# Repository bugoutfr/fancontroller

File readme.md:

# FanController

Standalone four-channel PWM fan controller based on the ESP32, with a local Windows client for Bluetooth Low Energy configuration and monitoring. No cloud service, account, or backend is required.

## Features

- Two 10 kΩ / B3950 NTC sensors, each assigned to two fans.
- Independent temperature profiles with linear interpolation.
- Per-fan PWM override and tachometer (TACH) speed measurement.
- Thermal protection takes priority over manual settings.
- Settings are applied in RAM and saved explicitly to NVS for persistence across restarts.
- BLE pairing is physically authorized with the ESP32 BOOT button.
- Windows client with profile charts, local 30-day temperature/RPM history, and system-tray operation.
- Automatic reconnection to the last Windows-paired controller. Interrupted writes are never replayed.

Temperature control runs on the ESP32 without a computer or Bluetooth connection. The percentage controls PWM duty cycle; it is not closed-loop RPM control.

## Project layout

| Directory | Contents | Guide |
|---|---|---|
| [esp32](esp32/) | Arduino / PlatformIO firmware, hardware configuration, and C++ tests | [Firmware guide](esp32/README.md) |
| [windows](windows/) | WinUI 3 / .NET 10 client for Windows 11 x64 and .NET tests | [Windows client guide](windows/README.md) |
| [hardware](hardware/) | KiCad prototype board CAD | [Hardware guide](hardware/README.md) |

The KiCad board is explicitly a work in progress and is **not ready for fabrication**. It does not replace the firmware wiring diagram.

## Quick start

### ESP32

From `esp32`, with PlatformIO installed:

```powershell
pio run -e esp32dev
pio run -e esp32dev -t upload
pio device monitor -b 115200
```

Review the [wiring and power precautions](esp32/README.md#wiring) before uploading. Do not connect powered USB and 5 V to VIN together unless supply isolation has been confirmed.

### Windows

From `windows`, with the prerequisites in the [Windows guide](windows/README.md):

```powershell
dotnet restore .\FanController.sln
dotnet test .\tests\FanController.Tests\FanController.Tests.csproj -c Release
dotnet publish .\src\FanController.App\FanController.App.csproj -c Release -r win-x64 -p:Platform=x64 -o .\artifacts\desktop
.\artifacts\desktop\FanController.App.exe
```

Distribute the complete publish directory, not only the executable.

## First pairing

1. Start the ESP32 normally, hold **BOOT for 2 seconds**, then release to open a 60-second pairing window.
2. Search for the controller in the Windows client and connect/pair.
3. Subsequent connections reuse the stored keys.

Holding **BOOT for 10 seconds** and releasing revokes the owner. Remove the Windows pairing before pairing again. Do not hold BOOT during reset. **Just Works** encrypts the link but does not protect the first pairing against active interception; pair in a trusted environment.

## License

This project is distributed under the permissive [MIT License](LICENSE). Third-party dependencies retain their own licenses; see the relevant dependency documentation.

## Tests

- Firmware and pairing tests: [ESP32 guide](esp32/README.md#build-and-test).
- Windows tests: [Windows guide](windows/README.md#build-test-and-run).

Host tests do not replace checking sensors, PWM/TACH outputs, Bluetooth, and power behavior on real hardware.

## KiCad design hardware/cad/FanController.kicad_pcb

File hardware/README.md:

# KiCad prototype board (P1)

> **Work in progress — NOT FOR FABRICATION.** A connected schematic and fully routed PCB are available, but the SATA connector mechanics and electrical qualifications still need review. No manufacturing outputs are approved.

## Open the design

Open `cad\FanController.kicad_pro` in **KiCad 10.0.7**.

- `cad\FanController.kicad_sch`: native A2 schematic with power, USB-UART, BOOT/RESET, four PWM/TACH channels, and two NTC inputs.
- `cad\FanController.kicad_pcb`: native two-layer board, 74 × 54 mm outline, four M2 mounting holes, and 71 electrical components.
- `cad\FanController.pretty\SATA_Power_B_Provisional.kicad_mod`: provisional custom SATA footprint; its mechanical fit is not confirmed.
- `cad\FanController.net` and `connectivity.json`: exported netlist and shared schematic/PCB pin-to-net manifest.
- `cad\FanController-schematic.pdf`, `cad\preview\`: design views, not manufacturing files.
- `cad\prototype-bom.csv`: design bill of materials, not an approved assembly BOM.

## Reproducible validation

From the repository root:

```powershell
.\hardware\cad\validate.ps1
```

This regenerates and overwrites the CAD files, restoring validated copper from `cad\routing.json`; it does not run the exploratory autorouter. Pad geometry and nets must match the routing source. The script uses the Python bundled with KiCad and has no external Python dependencies.

To validate the existing PCB without regenerating it:

```powershell
.\hardware\cad\validate.ps1 -Existing
```

The checked-in KiCad 10.0.7 validation reports 0 ERC errors/warnings, 0 physical DRC errors/warnings, 0 unconnected items, and 0 schematic parity differences. These results verify CAD consistency only; they do not qualify the board for manufacturing or safe operation.

After manually changing copper, run DRC before capturing the new route source:

```powershell
& 'C:\Program Files\KiCad\10.0\bin\kicad-cli.exe' pcb drc FanController.kicad_pcb --format json --output drc.json --schematic-parity --refill-zones --save-board --exit-code-violations
```

Only capture routing after a clean DRC:

```powershell
& 'C:\Program Files\KiCad\10.0\bin\python.exe' routing.py --capture
```

## Design constraints and open checks

- Target enclosure interior: 80 × 60 × 20 mm; board: 74 × 54 mm.
- Target MCU: ESP32-WROOM-32E-N4, 4 MB flash, no PSRAM. GPIO assignments must match [firmware HardwareConfig.h](../esp32/include/HardwareConfig.h).
- Four keyed PC fan headers, 12 V, 0.5 A per output and 2 A continuous aggregate (3 A startup target); actual fan current must be checked.
- Two JST-XH connectors for 10 kΩ / B3950 NTCs and fixed 10 kΩ resistors.
- USB-C USB 2.0, UART, BOOT, RESET. No RGB LED.
- SATA Power 15-contact device-side, right-angle type B connector. Verify electrical orientation, opposing locator, full body outline, and current rating against the actual part.

| Function | GPIO | ESP32-WROOM-32E module pin |
|---|---:|---:|
| PWM1 / TACH1 | 15 / 13 | 23 / 16 |
| PWM2 / TACH2 | 16 / 34 | 27 / 6 |
| PWM3 / TACH3 | 17 / 14 | 28 / 13 |
| PWM4 / TACH4 | 18 / 27 | 30 / 12 |
| NTC1 / NTC2 | 33 / 32 | 9 / 8 |
| RX0 / TX0 | 3 / 1 | 34 / 35 |
| BOOT / EN | 0 / EN | 25 / 3 |

The fan outputs use a 3.3 V logic stage and open-collector transistor to provide 5 V-compatible PWM. TACH uses a 5.23 kΩ pull-up to 3.3 V and 100 pF filter; never pull TACH up to 5 V. NTC inputs use a 10 kΩ divider and 100 nF filter. GPIO12 is pulled down to preserve the 3.3 V flash strapping level.

Power input ORing prevents reverse power flow through the rails but is **not galvanic isolation**. The USB behavior with the host powered off, UART margins at minimum USB voltage, USB current before enumeration, and LDO thermal dissipation remain to be qualified. Via-in-pad is a hand-soldered prototype assumption, not an industrial filled/plugged via specification.

The ESP32 antenna keepout, enclosure clearances, actual connector fit, fuses, startup current, and thermal behavior must be checked on a physical prototype. A clean DRC does not make this design production-ready.

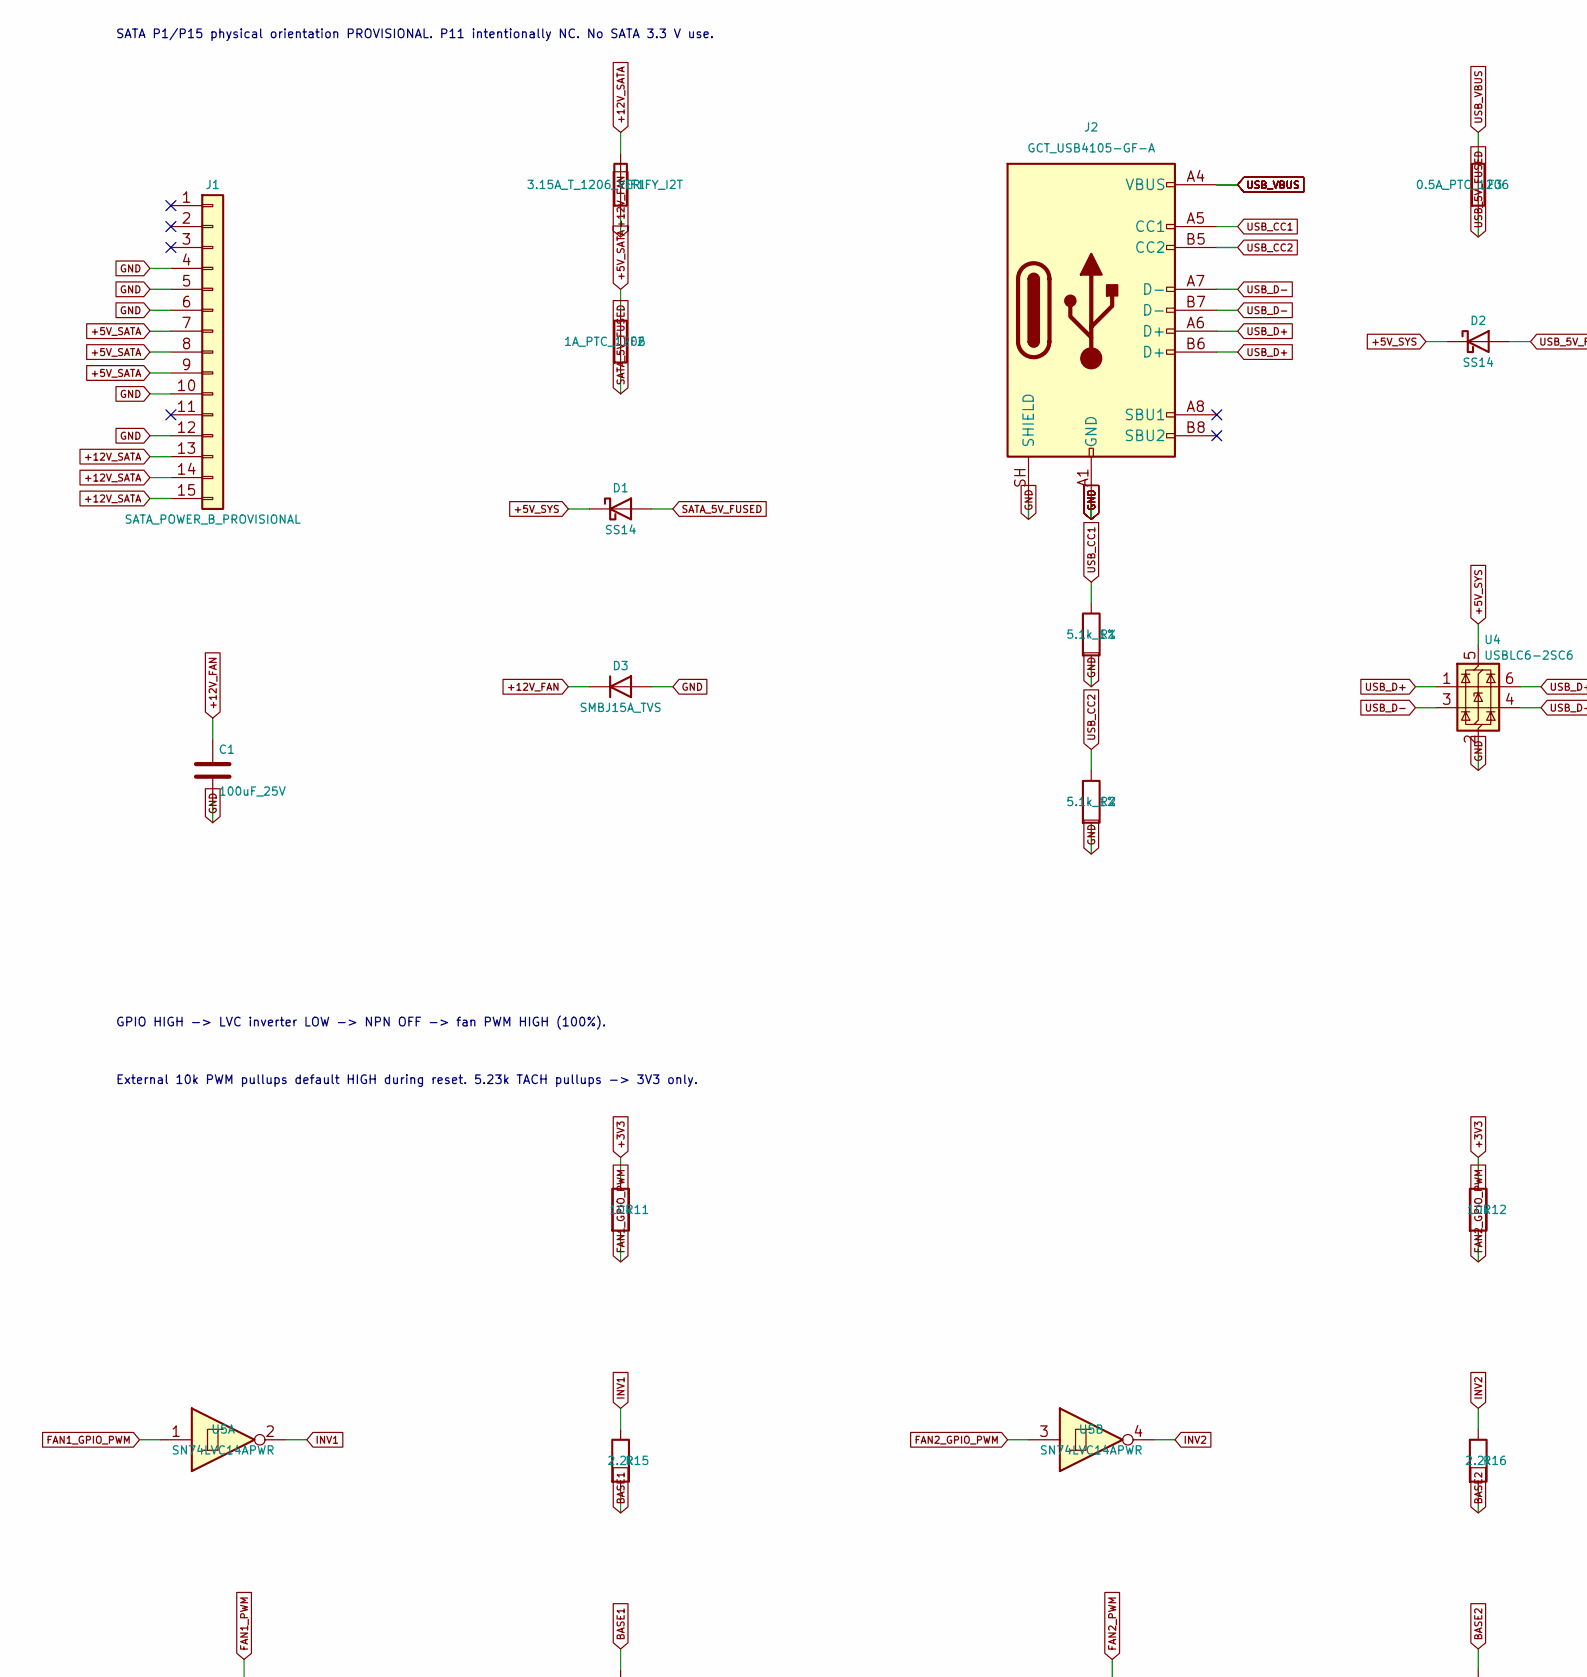
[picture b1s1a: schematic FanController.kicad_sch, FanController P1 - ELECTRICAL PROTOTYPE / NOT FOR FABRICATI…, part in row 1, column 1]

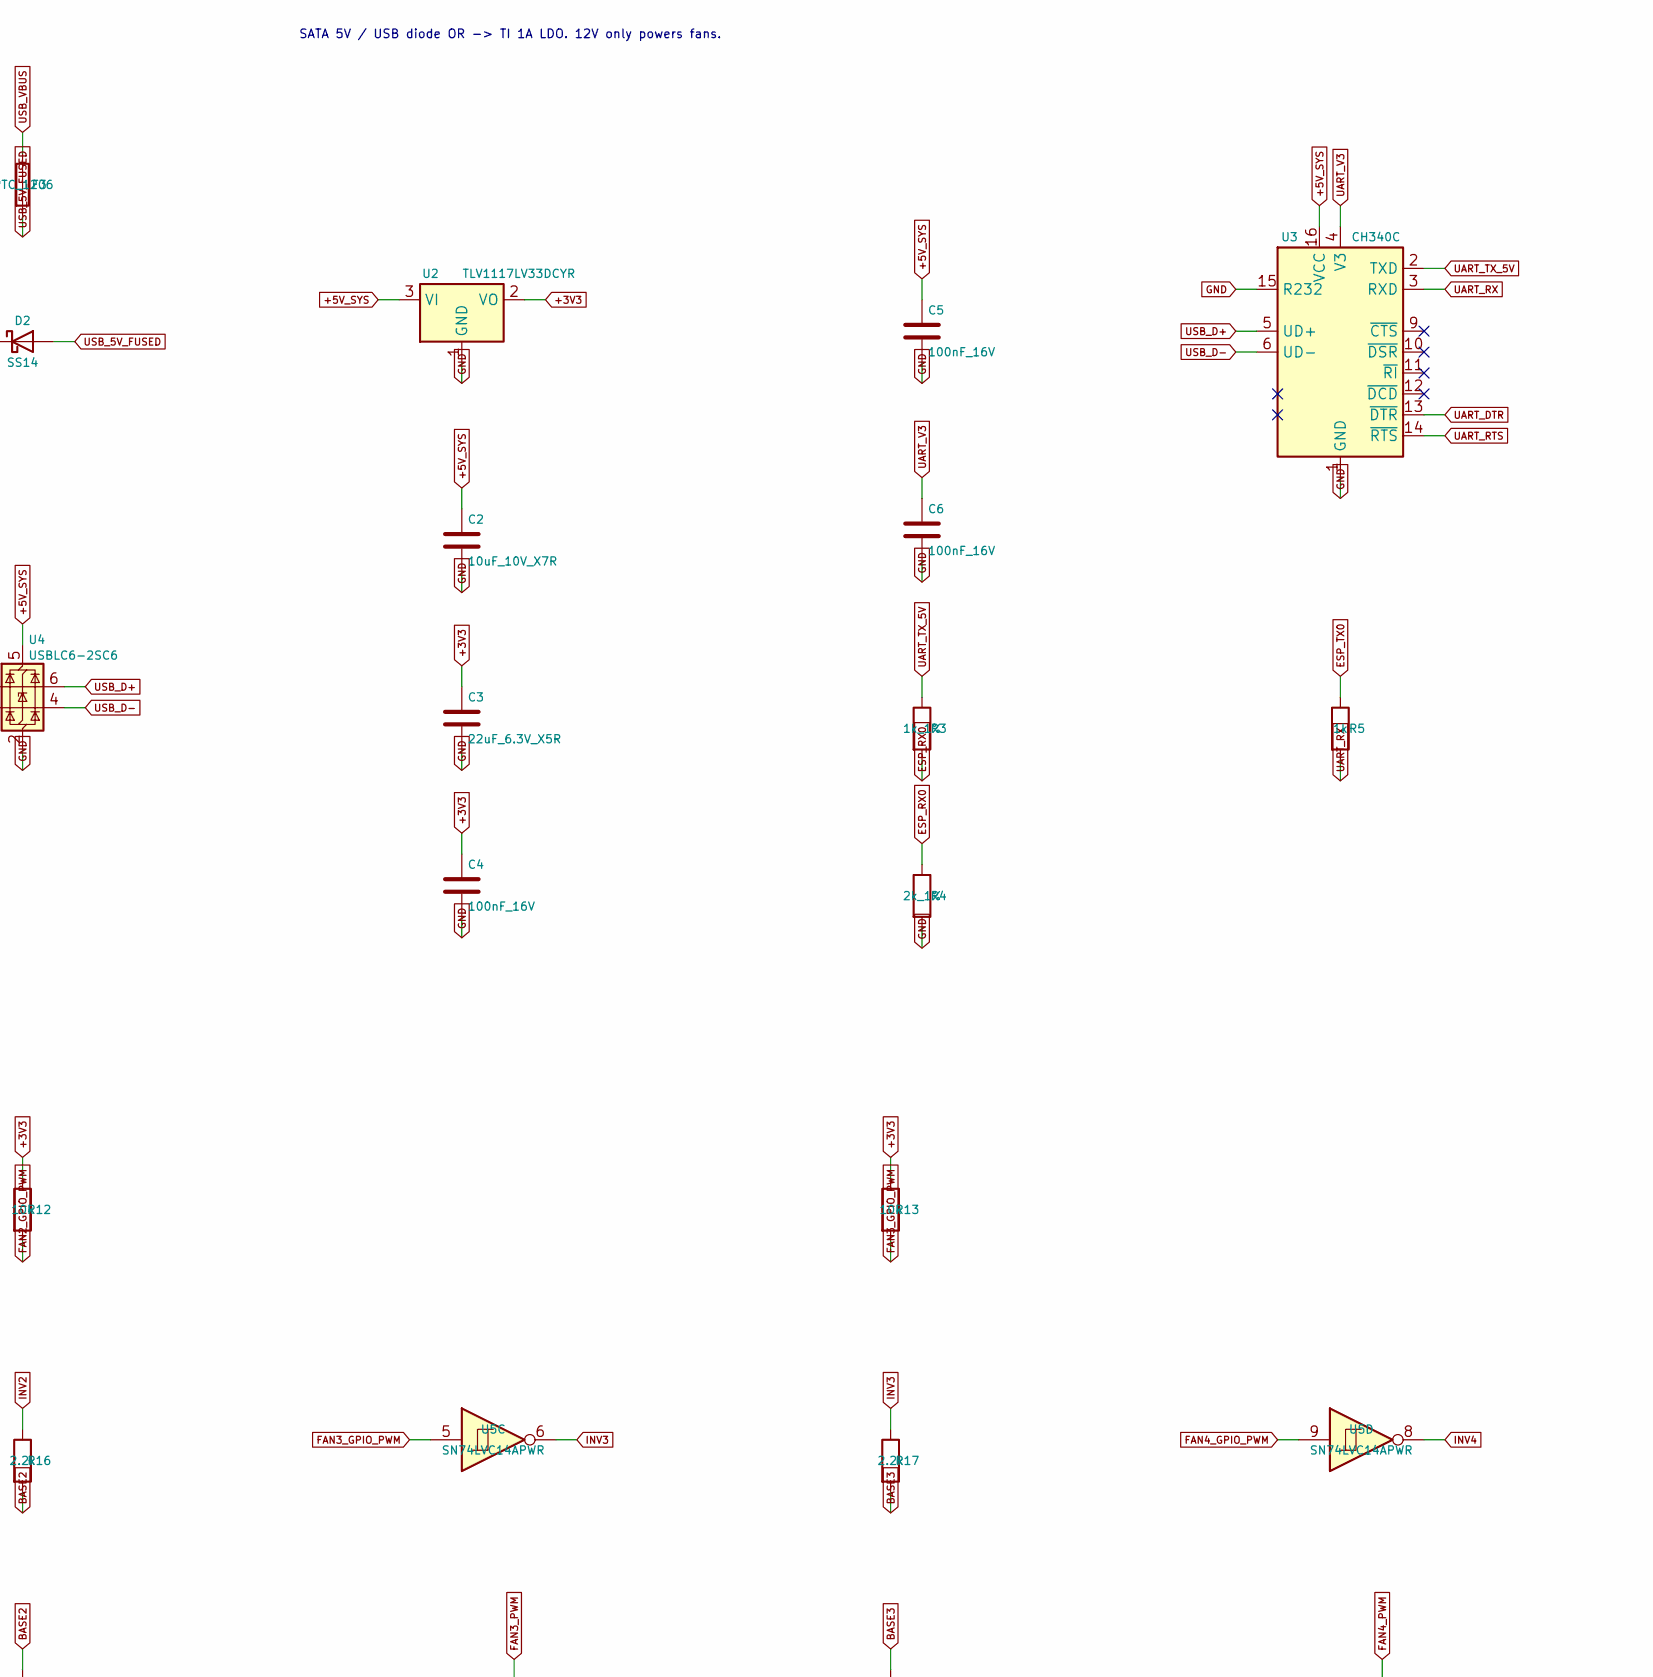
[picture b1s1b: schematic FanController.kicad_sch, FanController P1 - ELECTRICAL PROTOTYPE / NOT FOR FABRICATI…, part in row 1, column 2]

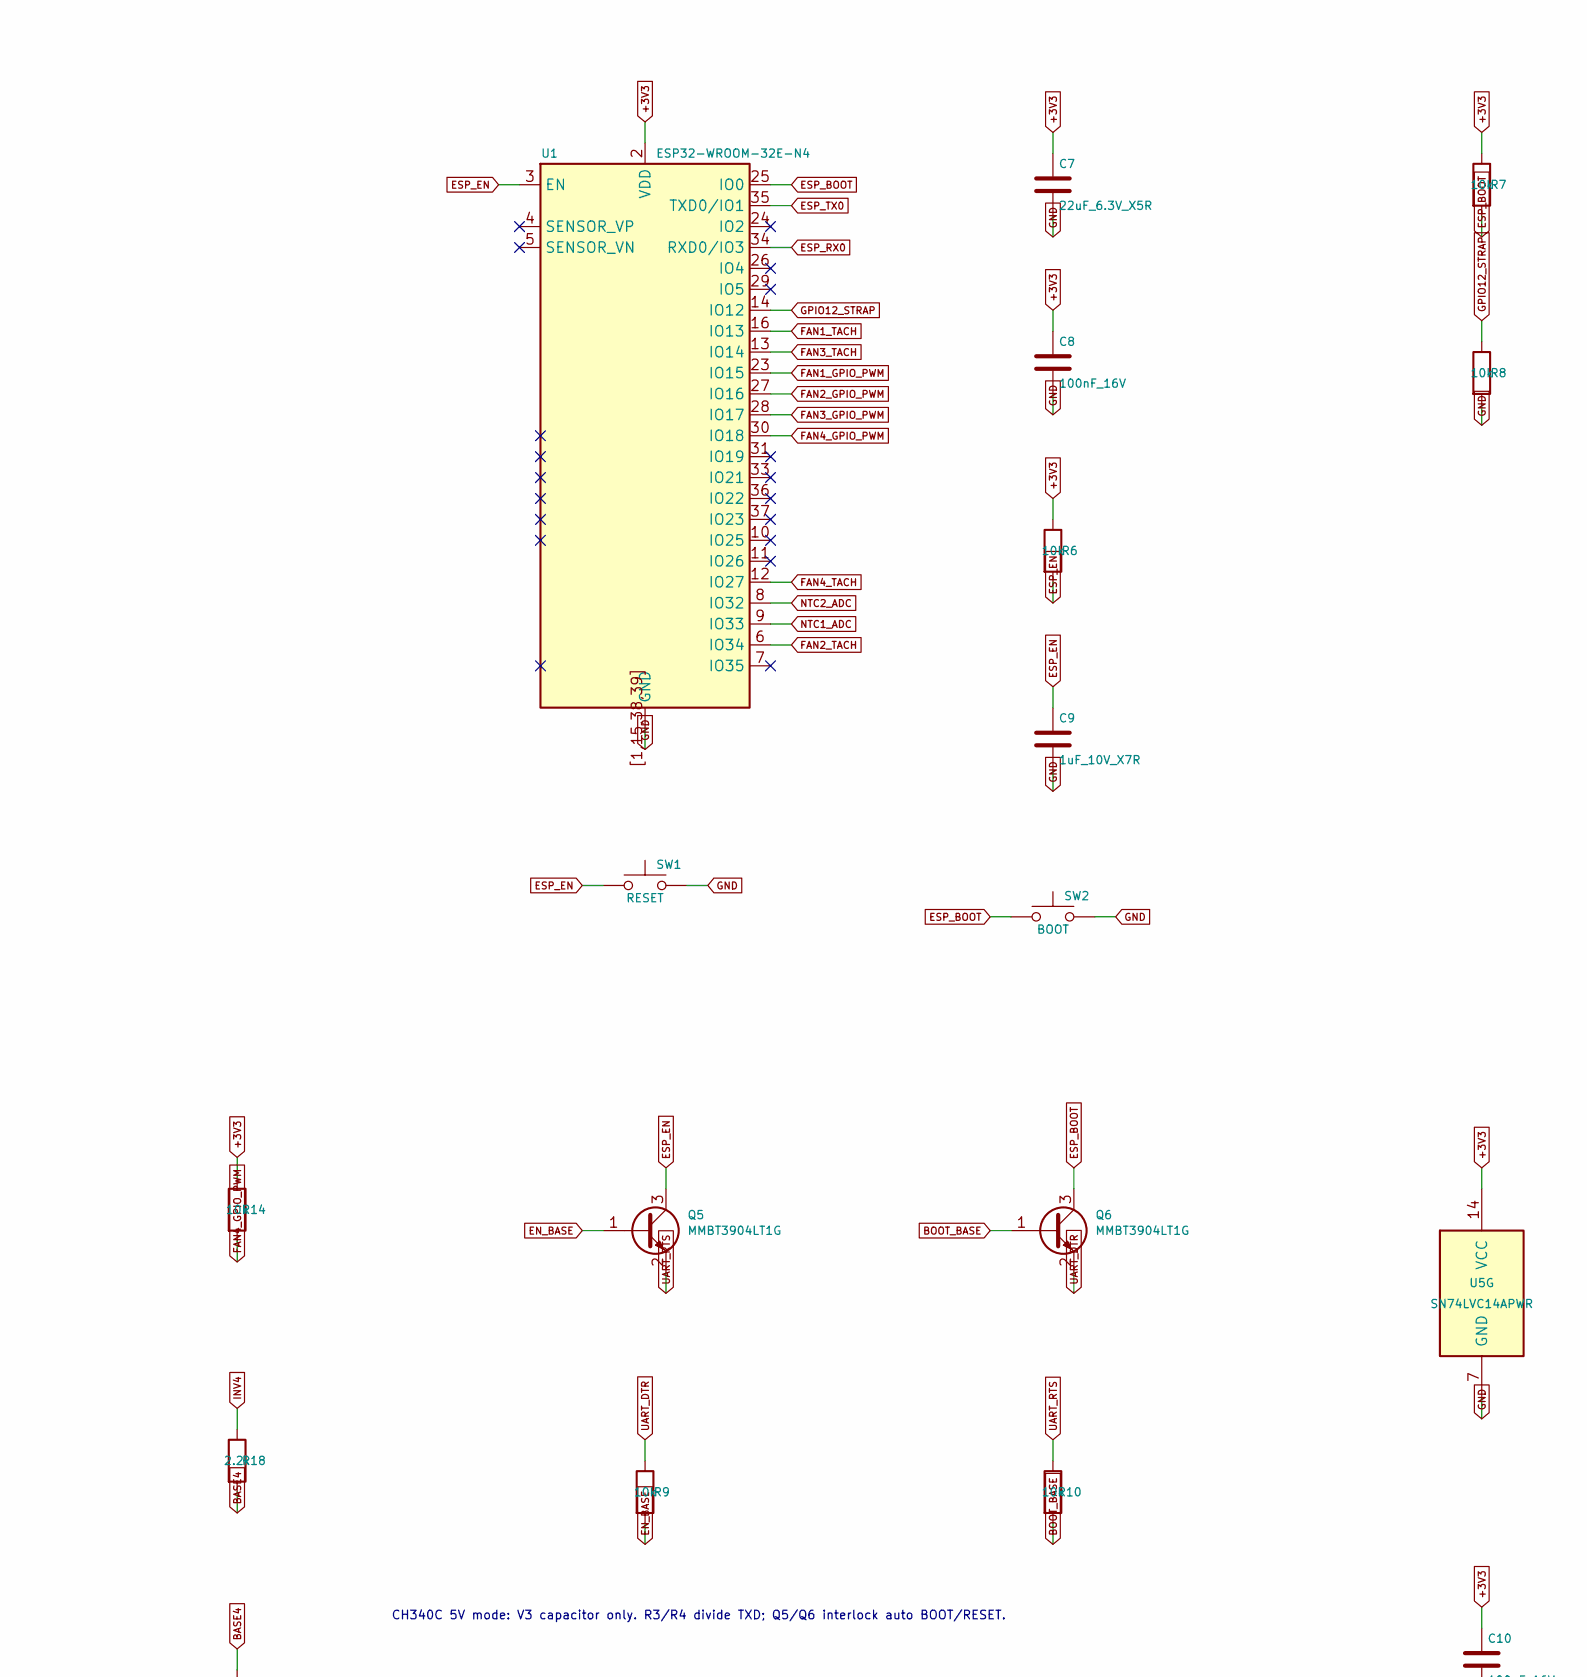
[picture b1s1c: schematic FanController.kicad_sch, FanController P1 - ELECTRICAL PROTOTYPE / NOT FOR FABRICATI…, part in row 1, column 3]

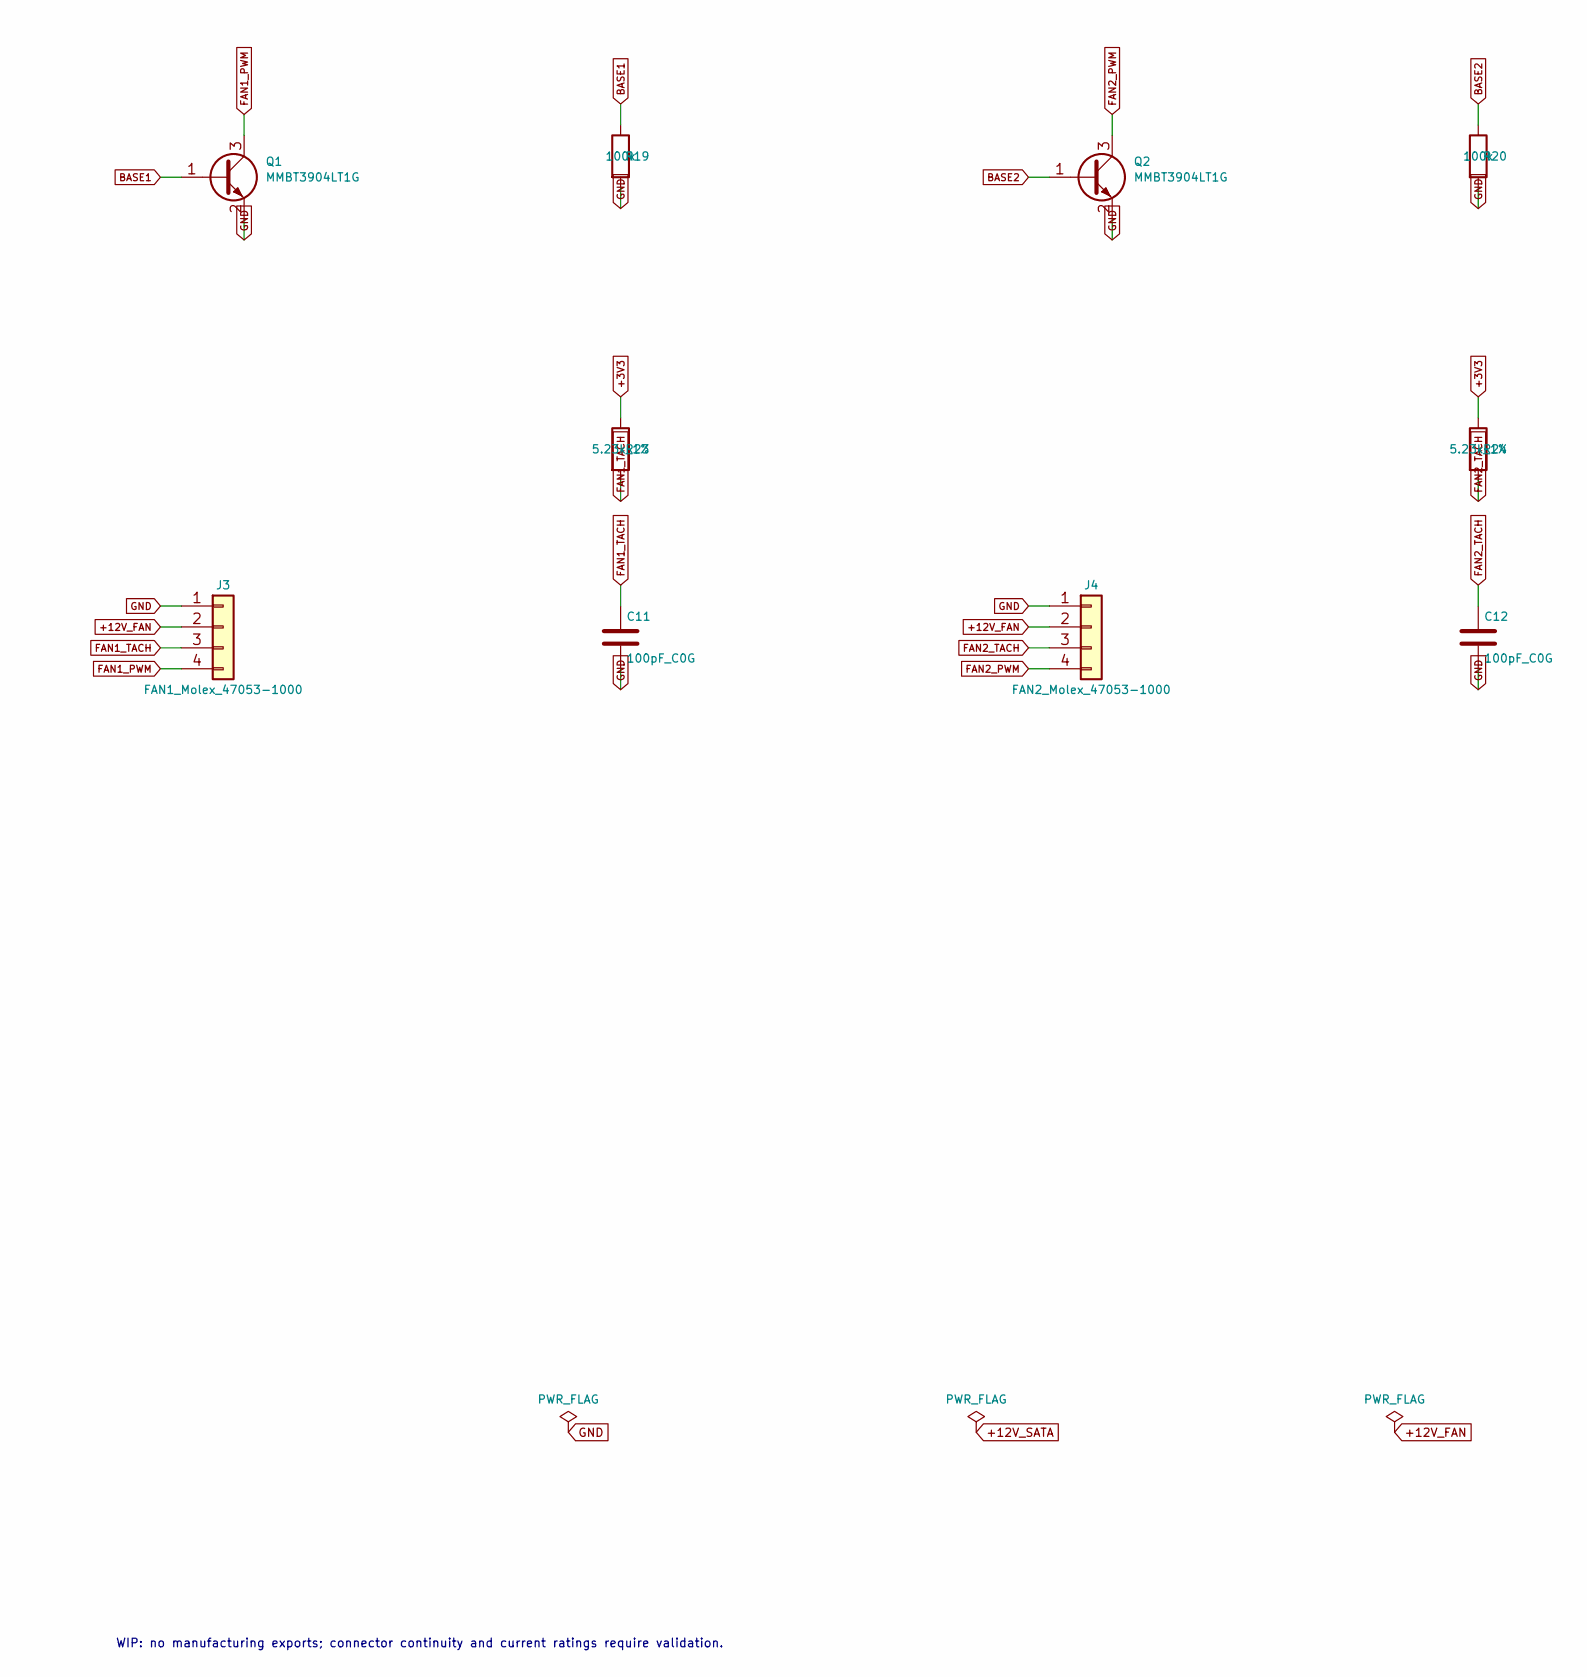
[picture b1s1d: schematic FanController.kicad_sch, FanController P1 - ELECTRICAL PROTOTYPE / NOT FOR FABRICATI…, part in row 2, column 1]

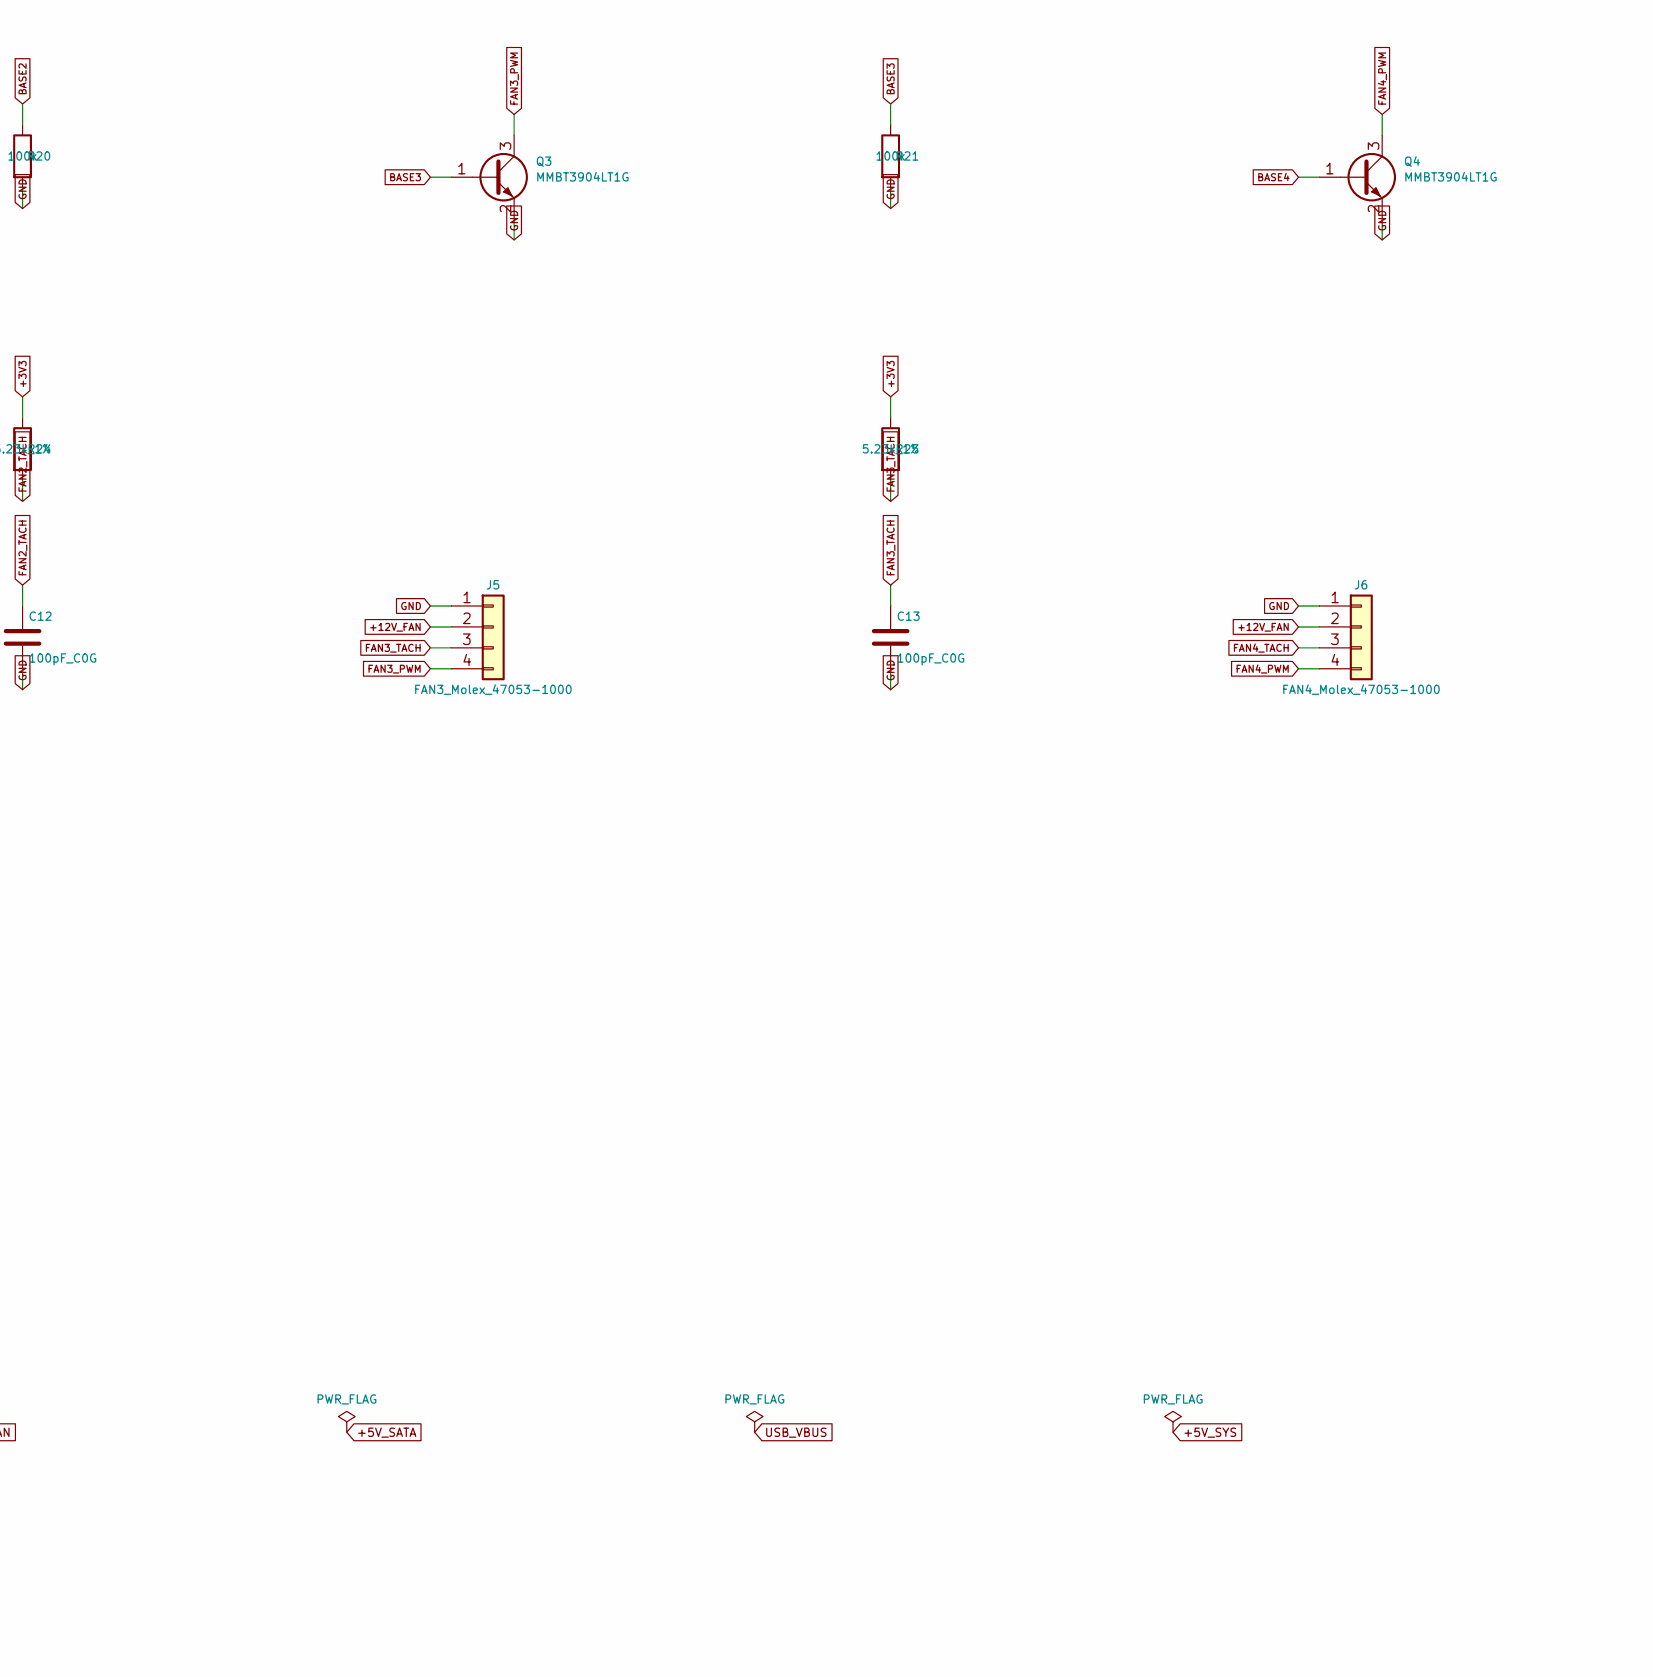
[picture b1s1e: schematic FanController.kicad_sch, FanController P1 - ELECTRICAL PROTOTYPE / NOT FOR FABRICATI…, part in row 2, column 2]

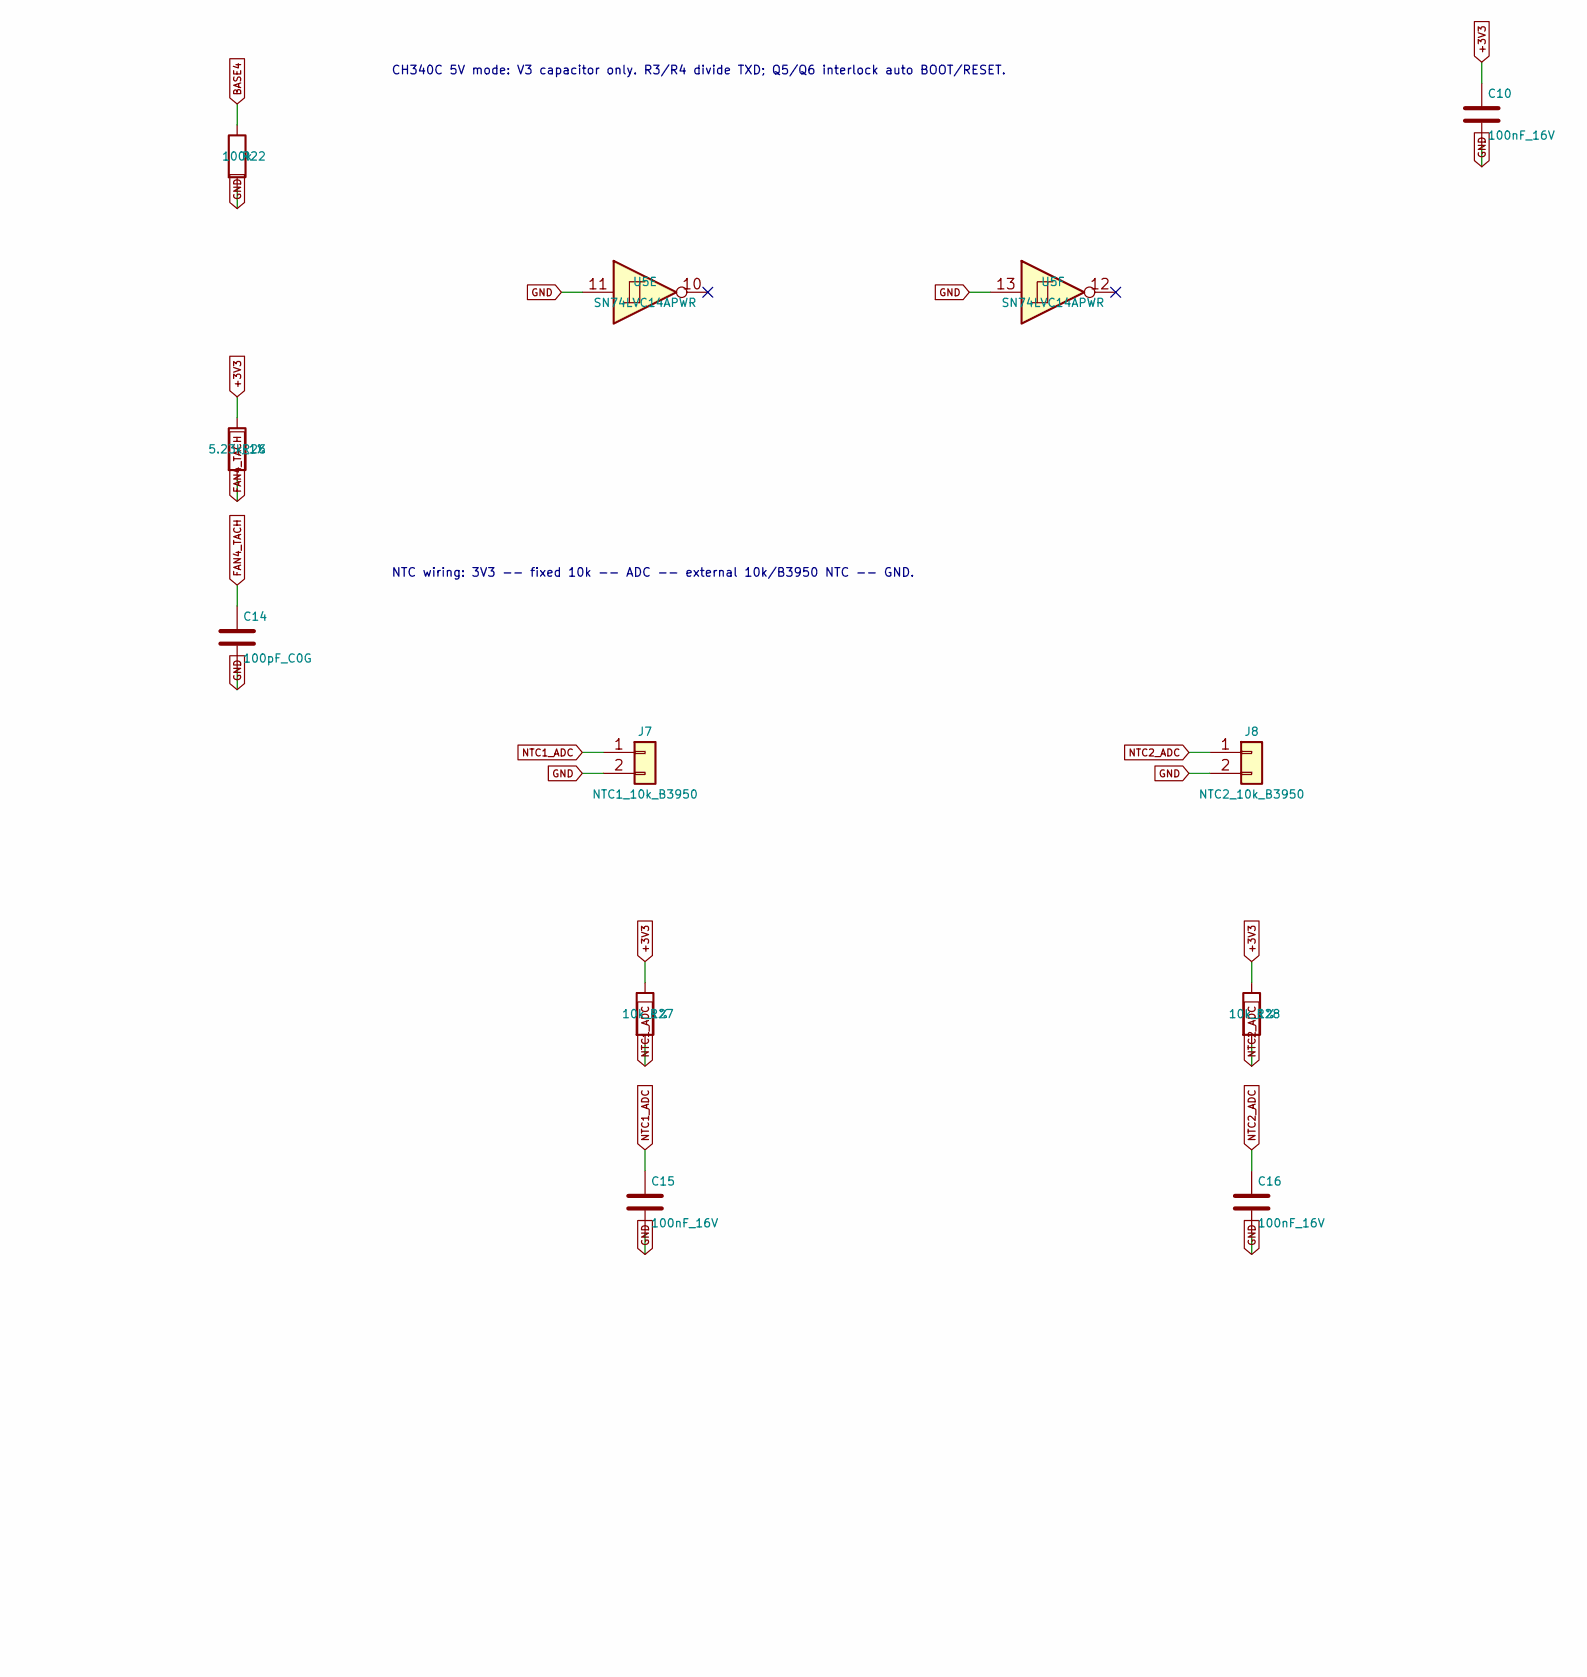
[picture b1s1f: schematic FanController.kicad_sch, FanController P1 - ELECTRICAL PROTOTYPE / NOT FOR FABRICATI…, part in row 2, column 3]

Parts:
C1: 100uF_25V; CP_Elec_6.3x7.7
C2: 10uF_10V_X7R; C_0805_2012Metric
C3, C7: 22uF_6.3V_X5R; C_0805_2012Metric
C4, C5, C6, C8, C10, C15, C16: 100nF_16V; C_0603_1608Metric
C9: 1uF_10V_X7R; C_0603_1608Metric
C11, C12, C13, C14: 100pF_C0G; C_0603_1608Metric
D1, D2: SS14; D_SMA
D3: SMBJ15A_TVS; D_SMB
F1: 3.15A_T_1206_VERIFY_I2T; Fuse_1206_3216Metric
F2: 1A_PTC_1206; Fuse_1206_3216Metric
F3: 0.5A_PTC_1206; Fuse_1206_3216Metric
J1: SATA_POWER_B_PROVISIONAL; SATA_Power_B_Provisional
J2: GCT_USB4105-GF-A; USB_C_Receptacle_GCT_USB4105-xx-A_16P_TopMnt_Horizontal
J3: FAN1_Molex_47053-1000; FanPinHeader_1x04_P2.54mm_Vertical
J4: FAN2_Molex_47053-1000; FanPinHeader_1x04_P2.54mm_Vertical
J5: FAN3_Molex_47053-1000; FanPinHeader_1x04_P2.54mm_Vertical
J6: FAN4_Molex_47053-1000; FanPinHeader_1x04_P2.54mm_Vertical
J7: NTC1_10k_B3950; JST_XH_B2B-XH-A_1x02_P2.50mm_Vertical
J8: NTC2_10k_B3950; JST_XH_B2B-XH-A_1x02_P2.50mm_Vertical
Q1, Q2, Q3, Q4, Q5, Q6: MMBT3904LT1G; SOT-23
R1, R2: 5.1k_1%; R_0603_1608Metric
R3: 1k_1%; R_0603_1608Metric
R4: 2k_1%; R_0603_1608Metric
R5: 1k; R_0603_1608Metric
R6, R7, R8, R9, R10, R11, R12, R13, R14: 10k; R_0603_1608Metric
R15, R16, R17, R18: 2.2k; R_0603_1608Metric
R19, R20, R21, R22: 100k; R_0603_1608Metric
R23, R24, R25, R26: 5.23k_1%; R_0603_1608Metric
R27, R28: 10k_1%; R_0603_1608Metric
SW1: RESET; SW_SPST_TL3342
SW2: BOOT; SW_SPST_TL3342
U1: ESP32-WROOM-32E-N4; ESP32-WROOM-32E
U2: TLV1117LV33DCYR; SOT-223-3_TabPin2
U3: CH340C; SOIC-16_3.9x9.9mm_P1.27mm
U4: USBLC6-2SC6; SOT-23-6
U5: SN74LVC14APWR; TSSOP-14_4.4x5mm_P0.65mm

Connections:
+3V3: C3.1, C4.1, C7.1, C8.1, C10.1, R6.1, R7.1, R11.1, R12.1, R13.1, R14.1, R23.1, R24.1, R25.1, R26.1, R27.1, R28.1, U1.2 (VDD), U2.2 (VO), U5.14 (VCC)
+5V_SATA: F2.1, J1.7, J1.8, J1.9
+5V_SYS: C2.1, C5.1, D1.1 (K), D2.1 (K), U2.3 (VI), U3.16 (VCC), U4.5 (VBUS)
+12V_FAN: C1.1, D3.1 (K), F1.2, J3.2, J4.2, J5.2, J6.2
+12V_SATA: F1.1, J1.13, J1.14, J1.15
BASE1: Q1.1 (B), R15.2, R19.1
BASE2: Q2.1 (B), R16.2, R20.1
BASE3: Q3.1 (B), R17.2, R21.1
BASE4: Q4.1 (B), R18.2, R22.1
BOOT_BASE: Q6.1 (B), R10.2
EN_BASE: Q5.1 (B), R9.2
ESP_BOOT: Q6.3 (C), R7.2, SW2.1, U1.25 (IO0)
ESP_EN: C9.1, Q5.3 (C), R6.2, SW1.1, U1.3 (EN)
ESP_RX0: R3.2, R4.1, U1.34 (RXD0/IO3)
ESP_TX0: R5.1, U1.35 (TXD0/IO1)
FAN1_GPIO_PWM: R11.2, U1.23 (IO15), U5.1
FAN1_PWM: J3.4, Q1.3 (C)
FAN1_TACH: C11.1, J3.3, R23.2, U1.16 (IO13)
FAN2_GPIO_PWM: R12.2, U1.27 (IO16), U5.3
FAN2_PWM: J4.4, Q2.3 (C)
FAN2_TACH: C12.1, J4.3, R24.2, U1.6 (IO34)
FAN3_GPIO_PWM: R13.2, U1.28 (IO17), U5.5
FAN3_PWM: J5.4, Q3.3 (C)
FAN3_TACH: C13.1, J5.3, R25.2, U1.13 (IO14)
FAN4_GPIO_PWM: R14.2, U1.30 (IO18), U5.9
FAN4_PWM: J6.4, Q4.3 (C)
FAN4_TACH: C14.1, J6.3, R26.2, U1.12 (IO27)
GND: C1.2, C2.2, C3.2, C4.2, C5.2, C6.2, C7.2, C8.2, C9.2, C10.2, C11.2, C12.2, C13.2, C14.2, C15.2, C16.2, D3.2 (A), J1.4, J1.5, J1.6, J1.10, J1.12, J2.A1 (GND), J2.A12 (GND), J2.B1 (GND), J2.B12 (GND), J2.SH (SHIELD), J3.1, J4.1, J5.1, J6.1, J7.2, J8.2, Q1.2 (E), Q2.2 (E), Q3.2 (E), Q4.2 (E), R1.2, R2.2, R4.2, R8.2, R19.2, R20.2, R21.2, R22.2, SW1.2, SW2.2, U1.1, U1.15, U1.38, U1.39, U1.[1,15,38,39] (GND), U2.1 (GND), U3.1 (GND), U3.15 (R232), U4.2 (GND), U5.7 (GND), U5.11, U5.13
GPIO12_STRAP: R8.1, U1.14 (IO12)
INV1: R15.1, U5.2
INV2: R16.1, U5.4
INV3: R17.1, U5.6
INV4: R18.1, U5.8
NTC1_ADC: C15.1, J7.1, R27.2, U1.9 (IO33)
NTC2_ADC: C16.1, J8.1, R28.2, U1.8 (IO32)
SATA_5V_FUSED: D1.2 (A), F2.2
UART_DTR: Q6.2 (E), R9.1, U3.13 (~DTR)
UART_RTS: Q5.2 (E), R10.1, U3.14 (~RTS)
UART_RX: R5.2, U3.3 (RXD)
UART_TX_5V: R3.1, U3.2 (TXD)
UART_V3: C6.1, U3.4 (V3)
USB_5V_FUSED: D2.2 (A), F3.2
USB_CC1: J2.A5 (CC1), R1.1
USB_CC2: J2.B5 (CC2), R2.1
USB_D+: J2.A6 (D+), J2.B6 (D+), U3.5 (UD+), U4.1 (I/O1), U4.6 (I/O1)
USB_D-: J2.A7 (D-), J2.B7 (D-), U3.6 (UD-), U4.3 (I/O2), U4.4 (I/O2)
USB_VBUS: F3.1, J2.A4 (VBUS), J2.A9 (VBUS), J2.B4 (VBUS), J2.B9 (VBUS)

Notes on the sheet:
SATA P1/P15 physical orientation PROVISIONAL. P11 intentionally NC. No SATA 3.3 V use.
SATA 5V / USB diode OR -> TI 1A LDO. 12V only powers fans.
GPIO HIGH -> LVC inverter LOW -> NPN OFF -> fan PWM HIGH (100%).
External 10k PWM pullups default HIGH during reset. 5.23k TACH pullups -> 3V3 only.
NTC wiring: 3V3 -- fixed 10k -- ADC -- external 10k/B3950 NTC -- GND.
CH340C 5V mode: V3 capacitor only. R3/R4 divide TXD; Q5/Q6 interlock auto BOOT/RESET.
WIP: no manufacturing exports; connector continuity and current ratings require validation.
